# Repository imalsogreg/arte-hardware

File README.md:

arte-hardware
=============

Arte hardware files.  Useful connector schematics and footprints, EIB designs, preamp designs, amp, etc

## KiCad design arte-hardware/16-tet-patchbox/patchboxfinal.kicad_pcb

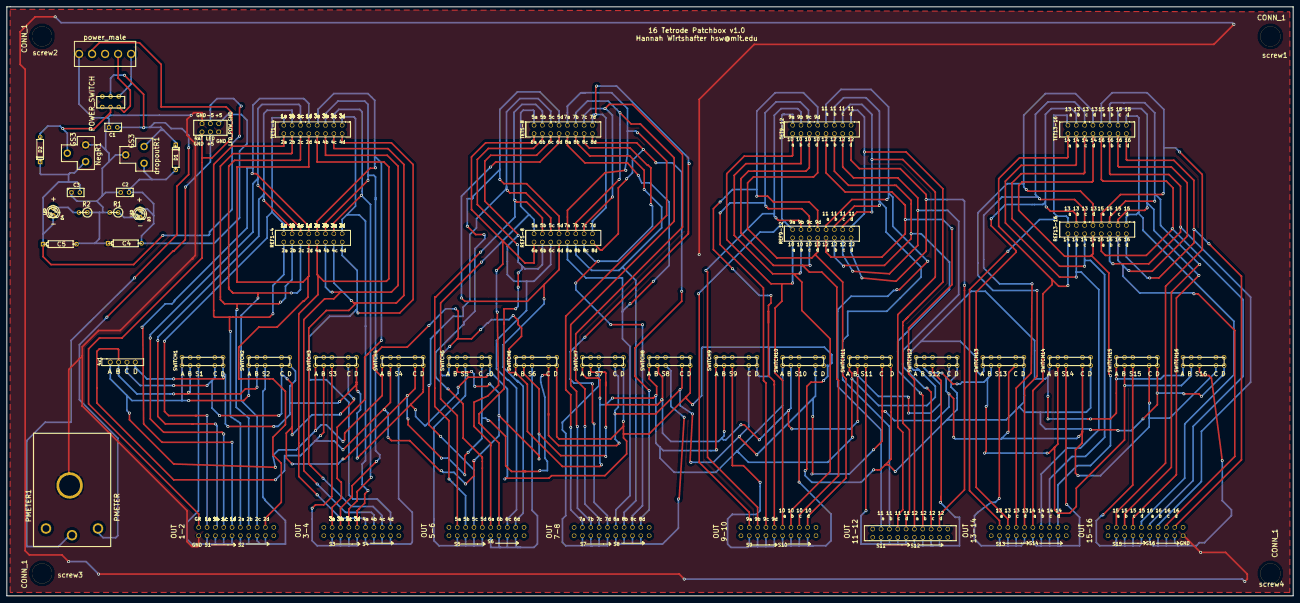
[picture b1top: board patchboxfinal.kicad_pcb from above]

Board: 2 copper layers, 391.7 x 179.3 mm, 18 parts (0 on the bottom side), 7 nets.

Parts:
C1, C2, C3: C; C1
C4, C5: CP; CP4
D1, D2: DIODE; D3
D3, D4: LED; LED-3MM
NegR1: GS3; negreg
PMETER1: PMETER
R1, R2: R; R1
dropoutR1: GS3; dropout
screw1, screw2, screw3, screw4: CONN_1; screw

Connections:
/+5: C2.1, C4.2, D1.1, D3.1, dropoutR1.3
/-5: C3.2, C5.1, D2.2, D4.2, NegR1.3
GND: C1.2, C2.2, C3.1, C4.1, C5.2, NegR1.1, PMETER1.4, R1.2, R2.1, dropoutR1.2
unnamed: D2.1, NegR1.2
unnamed: D3.2, R1.1
unnamed: D4.1, R2.2
unnamed: C1.1, D1.2, PMETER1.2, dropoutR1.1

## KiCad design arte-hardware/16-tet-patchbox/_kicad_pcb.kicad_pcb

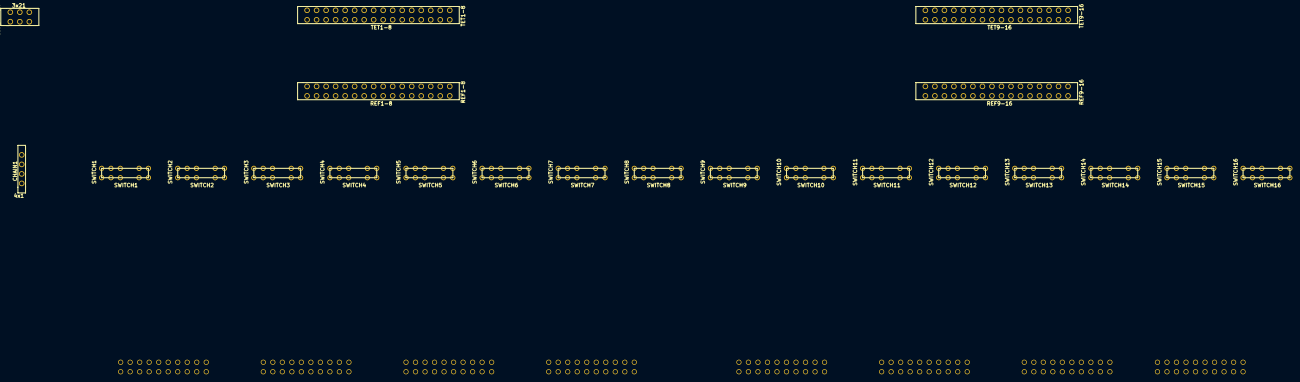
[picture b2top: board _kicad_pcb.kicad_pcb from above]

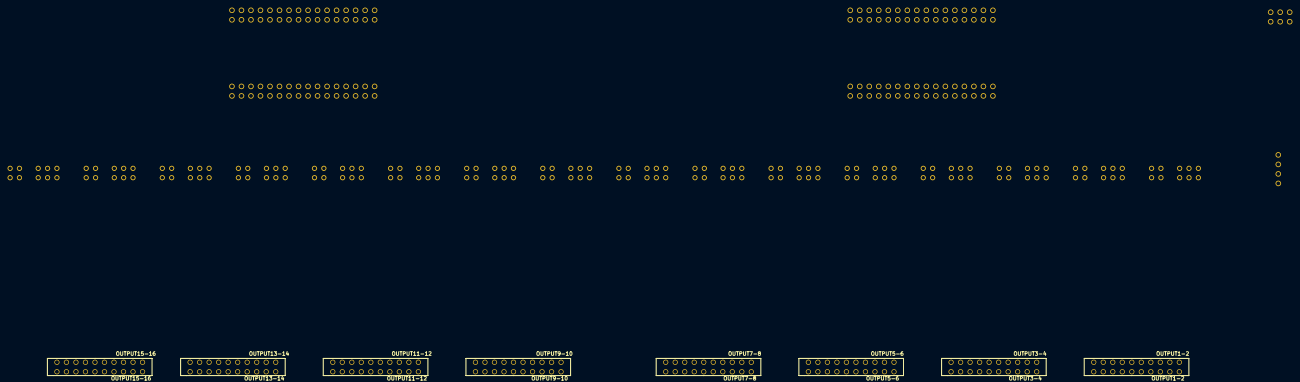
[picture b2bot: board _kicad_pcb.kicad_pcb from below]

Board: 2 copper layers, 30 parts (8 on the bottom side), 81 nets, no tracks yet.

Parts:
3x21: LED_POW_GND; IDC3x2
CHAIN1: 4x1; IDC4x1
OUTPUT1-2: OUTPUT1-2; IDC10x2correct
OUTPUT3-4: OUTPUT3-4; IDC10x2correct
OUTPUT5-6: OUTPUT5-6; IDC10x2correct
OUTPUT7-8: OUTPUT7-8; IDC10x2correct
OUTPUT9-10: OUTPUT9-10; IDC10x2correct
OUTPUT11-12: OUTPUT11-12; IDC10x2correct
OUTPUT13-14: OUTPUT13-14; IDC10x2correct
OUTPUT15-16: OUTPUT15-16; IDC10x2correct
REF1-8: REF1-8; idc16x2
REF9-16: REF9-16; idc16x2
SWITCH1: SWITCH1; Switch
SWITCH2: SWITCH2; Switch
SWITCH3: SWITCH3; Switch
SWITCH4: SWITCH4; Switch
SWITCH5: SWITCH5; Switch
SWITCH6: SWITCH6; Switch
SWITCH7: SWITCH7; Switch
SWITCH8: SWITCH8; Switch
SWITCH9: SWITCH9; Switch
SWITCH10: SWITCH10; Switch
SWITCH11: SWITCH11; Switch
SWITCH12: SWITCH12; Switch
SWITCH13: SWITCH13; Switch
SWITCH14: SWITCH14; Switch
SWITCH15: SWITCH15; Switch
SWITCH16: SWITCH16; Switch
TET1-8: TET1-8; idc16x2
TET9-16: TET9-16; idc16x2

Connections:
/1a: OUTPUT1-2.2, REF1-8.16, SWITCH1.1, TET1-8.16
/1b: OUTPUT1-2.3, REF1-8.15, SWITCH1.2, TET1-8.15
/1c: OUTPUT1-2.4, REF1-8.14, SWITCH1.3, TET1-8.14
/1d: OUTPUT1-2.5, REF1-8.13, SWITCH1.4, TET1-8.13
/2a: OUTPUT1-2.6, REF1-8.17, SWITCH2.1, TET1-8.17
/2b: OUTPUT1-2.7, REF1-8.18, SWITCH2.2, TET1-8.18
/2c: OUTPUT1-2.8, REF1-8.19, SWITCH2.3, TET1-8.19
/2d: OUTPUT1-2.9, REF1-8.20, SWITCH2.4, TET1-8.20
/3a: OUTPUT3-4.2, REF1-8.12, SWITCH3.1, TET1-8.12
/3b: OUTPUT3-4.3, REF1-8.11, SWITCH3.2, TET1-8.11
/3c: OUTPUT3-4.4, REF1-8.10, SWITCH3.3, TET1-8.10
/3d: OUTPUT3-4.5, REF1-8.9, SWITCH3.4, TET1-8.9
/4a: OUTPUT3-4.6, REF1-8.21, SWITCH4.1, TET1-8.21
/4b: OUTPUT3-4.7, REF1-8.22, SWITCH4.2, TET1-8.22
/4c: OUTPUT3-4.8, REF1-8.23, SWITCH4.3, TET1-8.23
/4d: OUTPUT3-4.9, REF1-8.24, SWITCH4.4, TET1-8.24
/5a: OUTPUT5-6.2, REF1-8.8, SWITCH5.1, TET1-8.8
/5b: OUTPUT5-6.3, REF1-8.7, SWITCH5.2, TET1-8.7
/5c: OUTPUT5-6.4, REF1-8.6, SWITCH5.3, TET1-8.6
/5d: OUTPUT5-6.5, REF1-8.5, SWITCH5.4, TET1-8.5
/6a: OUTPUT5-6.6, REF1-8.25, SWITCH6.1, TET1-8.25
/6b: OUTPUT5-6.7, REF1-8.26, SWITCH6.2, TET1-8.26
/6c: OUTPUT5-6.8, REF1-8.27, SWITCH6.3, TET1-8.27
/6d: OUTPUT5-6.9, REF1-8.28, SWITCH6.4, TET1-8.28
/7a: OUTPUT7-8.2, REF1-8.4, SWITCH7.1, TET1-8.4
/7b: OUTPUT7-8.3, REF1-8.3, SWITCH7.2, TET1-8.3
/7c: OUTPUT7-8.4, REF1-8.2, SWITCH7.3, TET1-8.2
/7d: OUTPUT7-8.5, REF1-8.1, SWITCH7.4, TET1-8.1
/8a: OUTPUT7-8.6, REF1-8.29, SWITCH8.1, TET1-8.29
/8b: OUTPUT7-8.7, REF1-8.30, SWITCH8.2, TET1-8.30
/8c: OUTPUT7-8.8, REF1-8.31, SWITCH8.3, TET1-8.31
/8d: OUTPUT7-8.9, REF1-8.32, SWITCH8.4, TET1-8.32
/9a: OUTPUT9-10.2, REF9-16.16, SWITCH9.1, TET9-16.16
/9b: OUTPUT9-10.3, REF9-16.15, SWITCH9.2, TET9-16.15
/9c: OUTPUT9-10.4, REF9-16.14, SWITCH9.3, TET9-16.14
/9d: OUTPUT9-10.5, REF9-16.13, SWITCH9.4, TET9-16.13
/10a: OUTPUT9-10.6, REF9-16.17, SWITCH10.1, TET9-16.17
/10b: OUTPUT9-10.7, REF9-16.18, SWITCH10.2, TET9-16.18
/10c: OUTPUT9-10.8, REF9-16.19, SWITCH10.3, TET9-16.19
/10d: OUTPUT9-10.9, REF9-16.20, SWITCH10.4, TET9-16.20
/11a: OUTPUT11-12.19, REF9-16.12, SWITCH11.1, TET9-16.12
/11b: OUTPUT11-12.18, REF9-16.11, SWITCH11.2, TET9-16.11
/11c: OUTPUT11-12.17, REF9-16.10, SWITCH11.3, TET9-16.10
/11d: OUTPUT11-12.16, REF9-16.9, SWITCH11.4, TET9-16.9
/12a: OUTPUT11-12.15, REF9-16.21, SWITCH12.1, TET9-16.21
/12b: OUTPUT11-12.14, REF9-16.22, SWITCH12.2, TET9-16.22
/12c: OUTPUT11-12.13, REF9-16.23, SWITCH12.3, TET9-16.23
/12d: OUTPUT11-12.12, REF9-16.24, SWITCH12.4, TET9-16.24
/13a: OUTPUT13-14.2, REF9-16.8, SWITCH13.1, TET9-16.8
/13b: OUTPUT13-14.3, REF9-16.7, SWITCH13.2, TET9-16.7
/13c: OUTPUT13-14.4, REF9-16.6, SWITCH13.3, TET9-16.6
/13d: OUTPUT13-14.5, REF9-16.5, SWITCH13.4, TET9-16.5
/14a: OUTPUT13-14.6, REF9-16.25, SWITCH14.1, TET9-16.25
/14b: OUTPUT13-14.7, REF9-16.26, SWITCH14.2, TET9-16.26
/14c: OUTPUT13-14.8, REF9-16.27, SWITCH14.3, TET9-16.27
/14d: OUTPUT13-14.9, REF9-16.28, SWITCH14.4, TET9-16.28
/15a: OUTPUT15-16.2, REF9-16.4, SWITCH15.1, TET9-16.4
/15b: OUTPUT15-16.3, REF9-16.3, SWITCH15.2, TET9-16.3
/15c: OUTPUT15-16.4, REF9-16.2, SWITCH15.3, TET9-16.2
/15d: OUTPUT15-16.5, REF9-16.1, SWITCH15.4, TET9-16.1
/16a: OUTPUT15-16.6, REF9-16.29, SWITCH16.1, TET9-16.29
/16b: OUTPUT15-16.7, REF9-16.30, SWITCH16.2, TET9-16.30
/16c: OUTPUT15-16.8, REF9-16.31, SWITCH16.3, TET9-16.31
/16d: OUTPUT15-16.9, REF9-16.32, SWITCH16.4, TET9-16.32
/s1: OUTPUT1-2.16, OUTPUT1-2.19, SWITCH1.5
/s2: OUTPUT1-2.12, OUTPUT1-2.15, SWITCH2.5
/s3: OUTPUT3-4.16, OUTPUT3-4.19, SWITCH3.5
/s4: OUTPUT3-4.11, SWITCH4.5
/s5: OUTPUT5-6.16, OUTPUT5-6.19, SWITCH5.5
/s6: OUTPUT5-6.12, OUTPUT5-6.15, SWITCH6.5
/s7: OUTPUT7-8.16, OUTPUT7-8.19
/s8: OUTPUT7-8.12, OUTPUT7-8.15
/s9: OUTPUT9-10.16, OUTPUT9-10.19, SWITCH9.5
/s10: OUTPUT9-10.12, OUTPUT9-10.15, SWITCH10.5
/s11: OUTPUT11-12.2, OUTPUT11-12.5, SWITCH11.5
/s12: OUTPUT11-12.6, OUTPUT11-12.9, SWITCH12.5
/s13: OUTPUT13-14.16, OUTPUT13-14.19
/s14: OUTPUT13-14.12, OUTPUT13-14.15, SWITCH14.5
/s15: OUTPUT15-16.16, OUTPUT15-16.19, SWITCH15.5
/s16: OUTPUT15-16.12, OUTPUT15-16.15, SWITCH16.5
unnamed: OUTPUT3-4.12, OUTPUT3-4.15

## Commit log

2014-01-28 Initial commit.
2014-02-25 almost done with the preamp. rearranged parts in directories
2014-03-13 First version of kikad eib and preamp files
2014-03-25 Upload before tweaking the eib hole position in the next version
2014-03-25 renaming, deleting inappropriately versioned gerber files
2014-03-26 Spread mount holes to 22.5mm. Shrink vias way down. EIB V4
2014-03-26 Plot preamp, change all version numbers to 4
2014-03-26 add svg prints of schematics for eib and preamp
2014-04-01 fix eib drill holes 10mil drill 20mil pad
2014-04-01 fix holes again on eib. 8 mil drill, 28 mill final diameter
2014-04-03 version 5 preamp - small vias, pads at board edge
2014-04-03 v5 add zip file
2014-04-14 Add solder mask gerbers to eib
2014-04-15 Add soldermask files eib_Mask_Front and eib_Mask_Back
2014-04-15 add zip file to get back into Sunstone batch
2014-04-18 added 16 tetrode patchbox
2014-04-18 organized files better
2014-04-29 updated board and fixed a bug in power circuit and ground islands
2016-06-30 added image file of schematic for easier futures
